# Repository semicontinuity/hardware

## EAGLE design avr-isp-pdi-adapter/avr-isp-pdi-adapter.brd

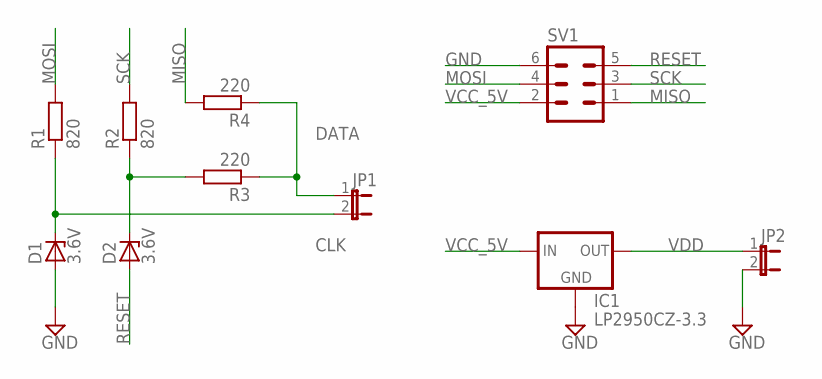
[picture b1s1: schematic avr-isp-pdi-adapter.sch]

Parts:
D1, D2: 3.6V; DO34Z7
IC1: LP2950CZ-3.3; TO92
JP1, JP2: JP1E; JP1
R1, R2: 820; 0207/10
R3, R4: 220; 0207/10
SV1: MA03-2

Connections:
CLK: D1.C, JP1.2, R1.1
DATA: JP1.1, R3.1, R4.1
GND: D1.A, IC1.2 (GND), JP2.2, SV1.6
MISO: R4.2, SV1.1
MOSI: R1.2, SV1.4
unnamed: D2.C, R2.1, R3.2
RESET: D2.A, SV1.5
SCK: R2.2, SV1.3
VCC_5V: IC1.3 (IN), SV1.2
VDD: IC1.1 (OUT), JP2.1

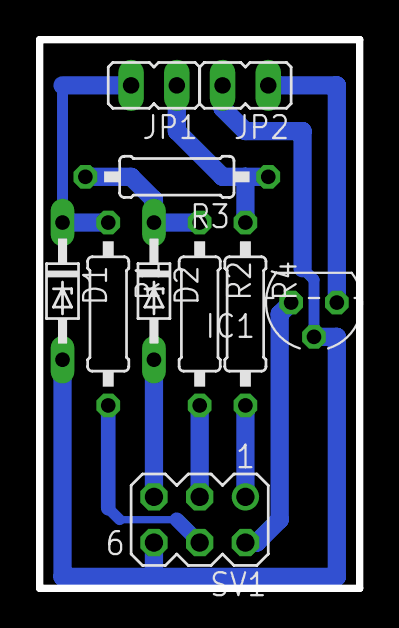
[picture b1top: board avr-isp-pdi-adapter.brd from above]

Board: 2 copper layers, 17.8 x 30.5 mm, 10 parts (0 on the bottom side), 10 nets.

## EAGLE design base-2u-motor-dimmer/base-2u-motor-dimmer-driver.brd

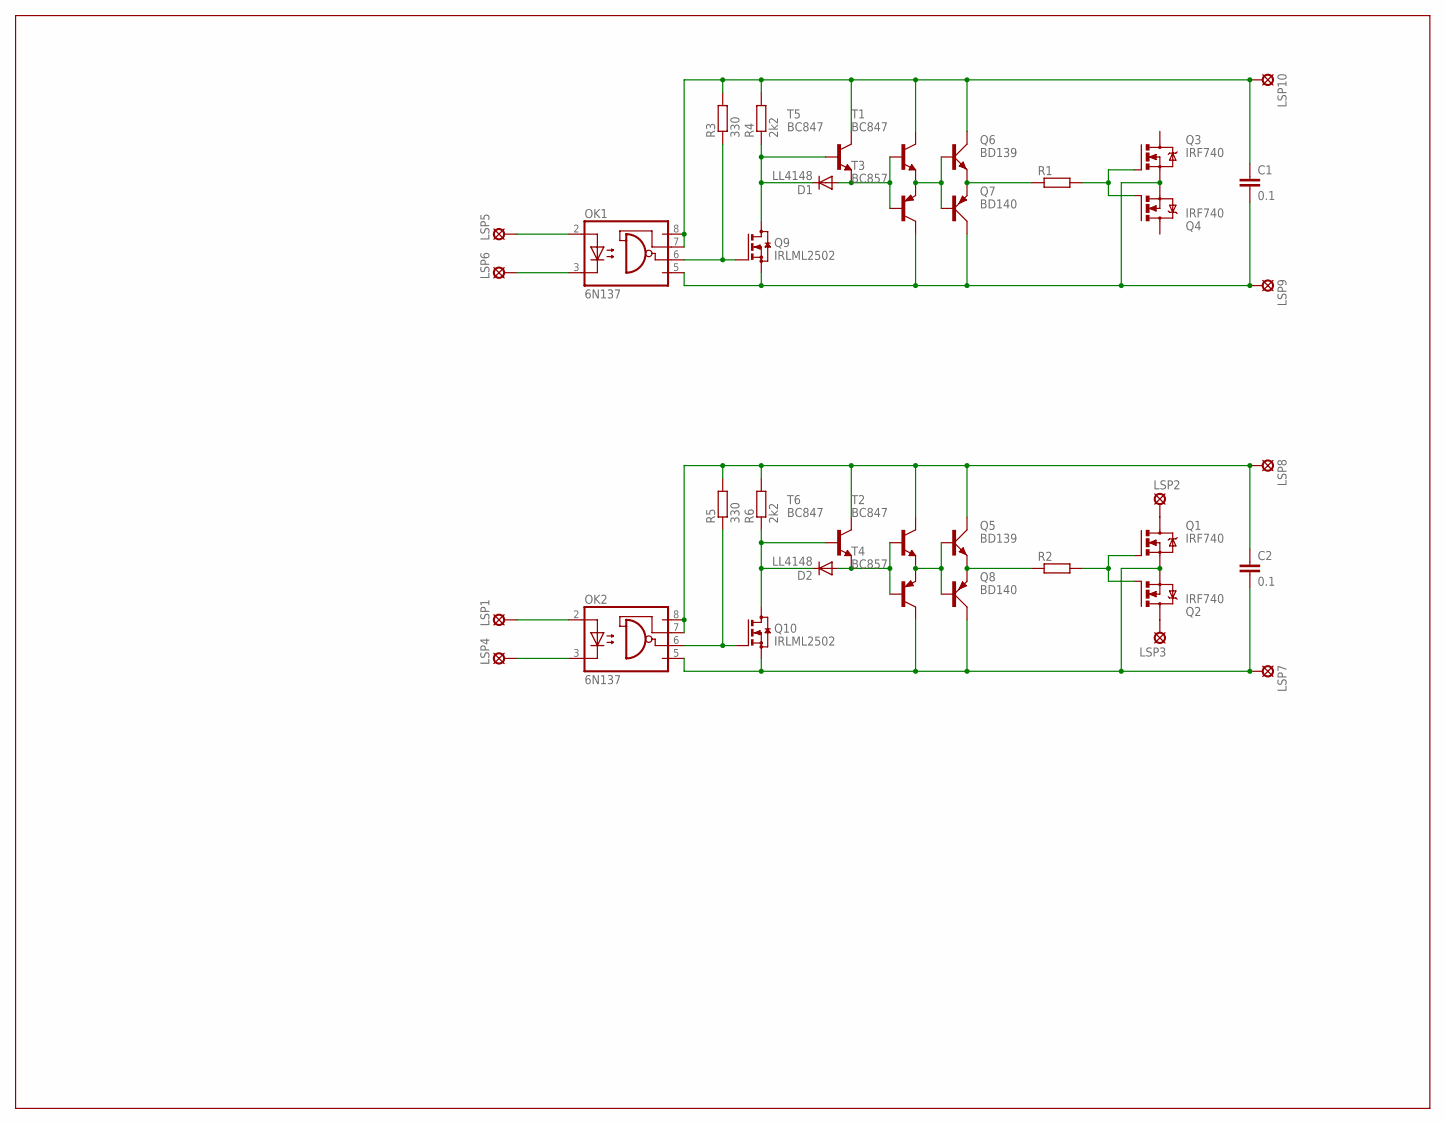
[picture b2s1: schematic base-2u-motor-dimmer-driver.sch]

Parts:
C1, C2: 0.1; C1206
D1, D2: LL4148; SOD80C
LSP1, LSP2, LSP3, LSP4, LSP5, LSP6, LSP7, LSP8, LSP9, LSP10: LSP10
OK1, OK2: 6N137; DIL08
Q1, Q2, Q3, Q4: IRF740; TO220BV
Q5, Q6: BD139; TO126AV
Q7, Q8: BD140; TO126AV
Q9, Q10: IRLML2502; SOT23
R1, R2: R-EU_R0805; R0805
R3, R5: 330; R0805
R4, R6: 2k2; R0805
T1, T2, T5, T6: BC847; SOT23
T3, T4: BC857; SOT23-BEC

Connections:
B_H: D1.A, T1.1 (B), T3.B, T5.2 (E)
B_L: D2.A, T2.1 (B), T4.B, T6.2 (E)
D_H: Q6.E, Q7.E, R1.1
D_L: Q5.E, Q8.E, R2.1
GND_H: C1.2, LSP9.MP, OK1.5 (GND), Q3.S, Q4.S, Q7.C, Q9.2 (S), T3.C
GND_L: C2.2, LSP7.MP, OK2.5 (GND), Q1.S, Q2.S, Q8.C, Q10.2 (S), T4.C
G_H: Q3.G, Q4.G, R1.2
G_L: Q1.G, Q2.G, R2.2
I_H: Q6.B, Q7.B, T1.2 (E), T3.E
I_L: Q5.B, Q8.B, T2.2 (E), T4.E
M_H: D1.C, Q9.3 (D), R4.1, T5.1 (B)
M_L: D2.C, Q10.3 (D), R6.1, T6.1 (B)
unnamed: LSP5.MP, OK1.2 (A)
unnamed: LSP6.MP, OK1.3 (C)
unnamed: LSP4.MP, OK2.3 (C)
unnamed: LSP2.MP, Q1.D
unnamed: LSP3.MP, Q2.D
unnamed: LSP1.MP, OK2.2 (A)
O_H: OK1.6 (VO), Q9.1 (G), R3.1
O_L: OK2.6 (VO), Q10.1 (G), R5.1
VCC1: C2.1, LSP8.MP, OK2.7 (VE), OK2.8 (VCC), Q5.C, R5.2, R6.2, T2.3 (C), T6.3 (C)
VCC_H: C1.1, LSP10.MP, OK1.7 (VE), OK1.8 (VCC), Q6.C, R3.2, R4.2, T1.3 (C), T5.3 (C)

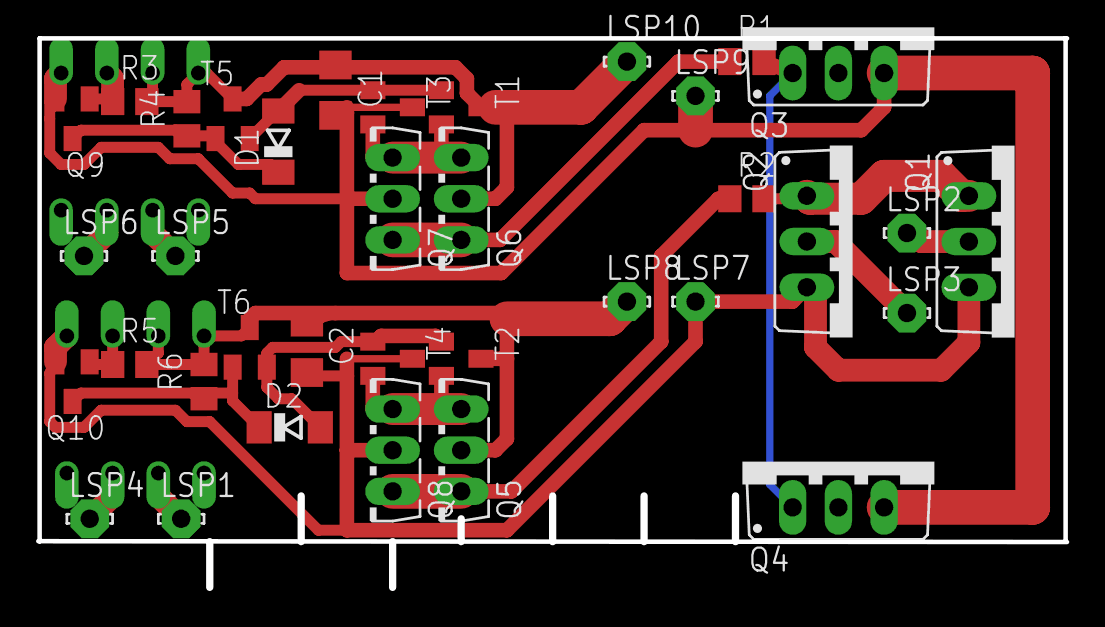
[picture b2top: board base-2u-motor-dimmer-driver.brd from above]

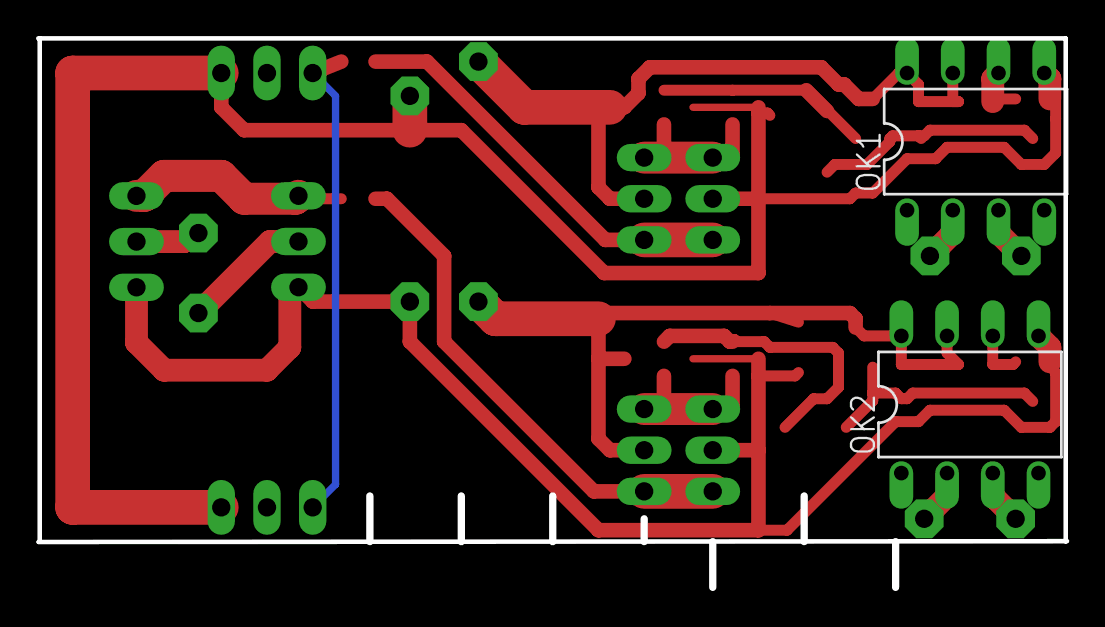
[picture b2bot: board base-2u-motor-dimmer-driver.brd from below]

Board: 2 copper layers, 57.2 x 30.5 mm, 38 parts (2 on the bottom side), 22 nets.
